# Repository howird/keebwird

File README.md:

# keebwird

low-profile, column-staggered, unibody, 34 key mechanical keyboard based on the ferris sweep

custom symbols and footprints from [MX_Alps_Hybrid](https://github.com/ai03-2725/MX_Alps_Hybrid) and [Keebio](https://github.com/keebio)

QMK firmware can be found [here](https://github.com/howird/keebwird_firmware)
 
 # BOM
| Name                             | Quantity          |
|----------------------------------|-------------------|
| Arduino Pro Micro                | 1 |
| General-purpose diode (DO-35)    | 34 |
| Kailh Choc Switches              | 34 |
| Choc Keycaps                     | 34 |
| Reset Swich  (Optional)          | 1 |

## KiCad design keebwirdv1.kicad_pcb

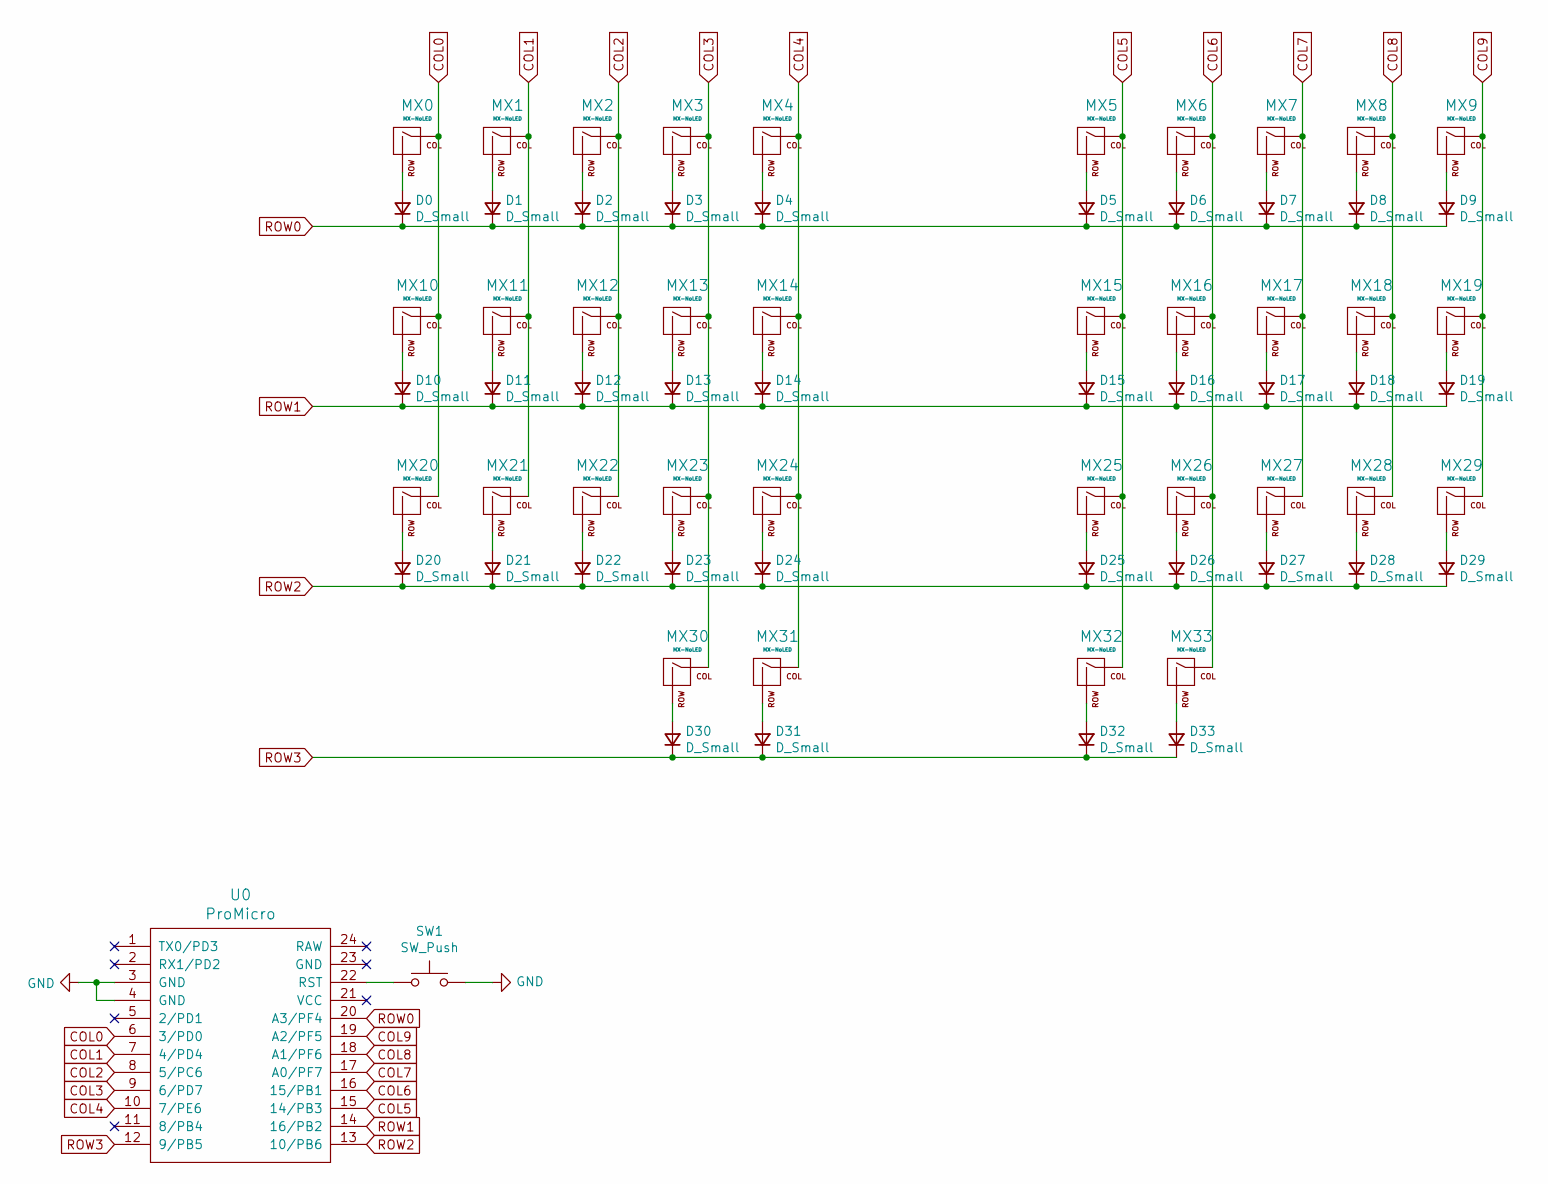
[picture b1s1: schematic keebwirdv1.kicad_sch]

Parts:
D0, D1, D2, D3, D4, D5, D6, D7, D8, D9, D10, D11, D12, D13, D14, D15, D16, D17, D18, D19, D20, D21, D22, D23, D24, D25, D26, D27, D28, D29, D30, D31, D32, D33: D_Small; Diode
MX0, MX1, MX2, MX3, MX4, MX5, MX6, MX7, MX8, MX9, MX10, MX11, MX12, MX13, MX14, MX15, MX16, MX17, MX18, MX19, MX20, MX21, MX22, MX23, MX24, MX25, MX26, MX27, MX28, MX29, MX30, MX31, MX32, MX33: MX-NoLED; KailhChoc-1U
SW1: SW_Push; ResetSW_1side
U0: ProMicro; ArduinoProMicro

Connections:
COL0: MX0.1 (COL), MX10.1 (COL), MX20.1 (COL), U0.6 (3/PD0)
COL1: MX1.1 (COL), MX11.1 (COL), MX21.1 (COL), U0.7 (4/PD4)
COL2: MX2.1 (COL), MX12.1 (COL), MX22.1 (COL), U0.8 (5/PC6)
COL3: MX3.1 (COL), MX13.1 (COL), MX23.1 (COL), MX30.1 (COL), U0.9 (6/PD7)
COL4: MX4.1 (COL), MX14.1 (COL), MX24.1 (COL), MX31.1 (COL), U0.10 (7/PE6)
COL5: MX5.1 (COL), MX15.1 (COL), MX25.1 (COL), MX32.1 (COL), U0.15 (14/PB3)
COL6: MX6.1 (COL), MX16.1 (COL), MX26.1 (COL), MX33.1 (COL), U0.16 (15/PB1)
COL7: MX7.1 (COL), MX17.1 (COL), MX27.1 (COL), U0.17 (A0/PF7)
COL8: MX8.1 (COL), MX18.1 (COL), MX28.1 (COL), U0.18 (A1/PF6)
COL9: MX9.1 (COL), MX19.1 (COL), MX29.1 (COL), U0.19 (A2/PF5)
GND: SW1.2, U0.3 (GND), U0.4 (GND)
unnamed: D0.2 (A), MX0.2 (ROW)
unnamed: D1.2 (A), MX1.2 (ROW)
unnamed: D2.2 (A), MX2.2 (ROW)
unnamed: D3.2 (A), MX3.2 (ROW)
unnamed: D4.2 (A), MX4.2 (ROW)
unnamed: D5.2 (A), MX5.2 (ROW)
unnamed: D6.2 (A), MX6.2 (ROW)
unnamed: D7.2 (A), MX7.2 (ROW)
unnamed: D8.2 (A), MX8.2 (ROW)
unnamed: D9.2 (A), MX9.2 (ROW)
unnamed: D10.2 (A), MX10.2 (ROW)
unnamed: D11.2 (A), MX11.2 (ROW)
unnamed: D12.2 (A), MX12.2 (ROW)
unnamed: D13.2 (A), MX13.2 (ROW)
unnamed: D14.2 (A), MX14.2 (ROW)
unnamed: D15.2 (A), MX15.2 (ROW)
unnamed: D16.2 (A), MX16.2 (ROW)
unnamed: D17.2 (A), MX17.2 (ROW)
unnamed: D18.2 (A), MX18.2 (ROW)
unnamed: D19.2 (A), MX19.2 (ROW)
unnamed: D20.2 (A), MX20.2 (ROW)
unnamed: D21.2 (A), MX21.2 (ROW)
unnamed: D22.2 (A), MX22.2 (ROW)
unnamed: D23.2 (A), MX23.2 (ROW)
unnamed: D24.2 (A), MX24.2 (ROW)
unnamed: D25.2 (A), MX25.2 (ROW)
unnamed: D26.2 (A), MX26.2 (ROW)
unnamed: D27.2 (A), MX27.2 (ROW)
unnamed: D28.2 (A), MX28.2 (ROW)
unnamed: D29.2 (A), MX29.2 (ROW)
unnamed: D30.2 (A), MX30.2 (ROW)
unnamed: D31.2 (A), MX31.2 (ROW)
unnamed: D32.2 (A), MX32.2 (ROW)
unnamed: D33.2 (A), MX33.2 (ROW)
unnamed: SW1.1, U0.22 (RST)
ROW0: D0.1 (K), D1.1 (K), D2.1 (K), D3.1 (K), D4.1 (K), D5.1 (K), D6.1 (K), D7.1 (K), D8.1 (K), D9.1 (K), U0.20 (A3/PF4)
ROW1: D10.1 (K), D11.1 (K), D12.1 (K), D13.1 (K), D14.1 (K), D15.1 (K), D16.1 (K), D17.1 (K), D18.1 (K), D19.1 (K), U0.14 (16/PB2)
ROW2: D20.1 (K), D21.1 (K), D22.1 (K), D23.1 (K), D24.1 (K), D25.1 (K), D26.1 (K), D27.1 (K), D28.1 (K), D29.1 (K), U0.13 (10/PB6)
ROW3: D30.1 (K), D31.1 (K), D32.1 (K), D33.1 (K), U0.12 (9/PB5)

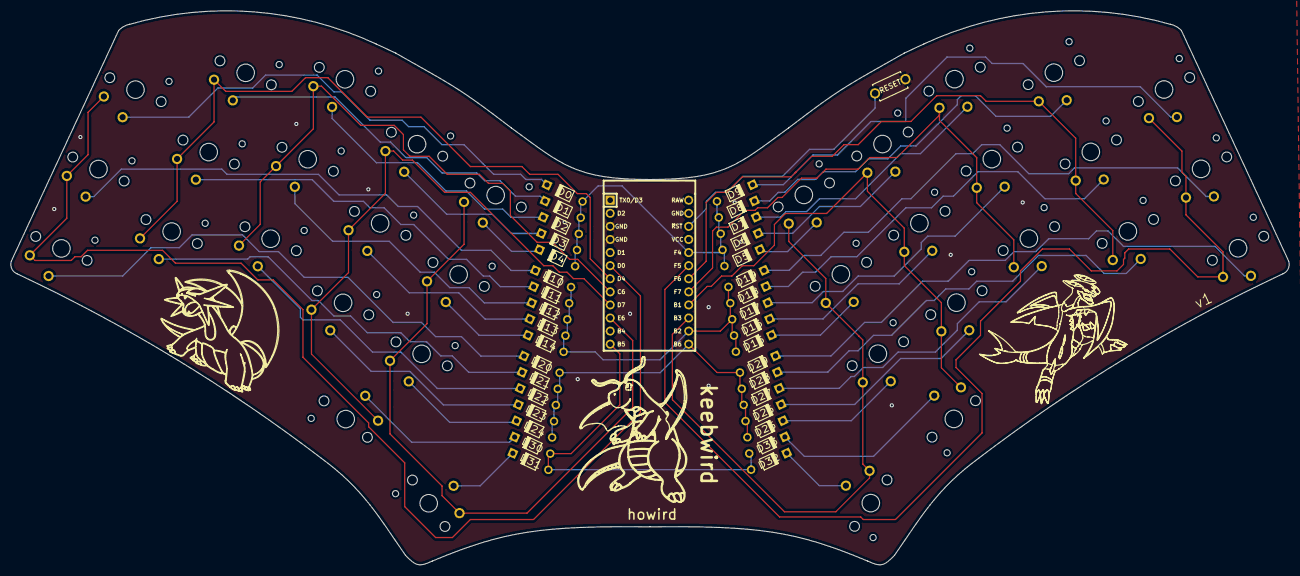
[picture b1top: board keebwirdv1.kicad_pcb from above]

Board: 2 copper layers, 248.1 x 107.5 mm, 70 parts (0 on the bottom side), 50 nets.

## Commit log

2021-10-22 removed extra files
2021-10-23 keebwird.kicad_pcb
2021-10-23 updated symbol and footprint libraries
2021-10-23 Drop files from .gitignore
2021-10-23 added silkscreen pokemon
2021-10-23 updated silkscreen
2021-10-23 updated gerbers
2021-10-23 added gerber zip
2021-11-06 added grounding vias, added lightcycle keeb openscad
2021-12-22 added vias to ground planes
2021-12-22 updated photo
2021-12-22 updated gitignore
2021-12-22 updated gerber files
2021-12-23 added drills to gerber
2022-02-10 added real photo and firmware to readme
2022-02-10 typo
